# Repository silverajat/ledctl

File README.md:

# ledctl: an FPGA music-sync LED controller

A board I designed from scratch that turns music into a light show on a 115-LED addressable strip.
The laptop listens to what's playing (Spotify or anything else), works out the beat, the bars, the drums,
the genre and where the song is going (build-up, drop, breakdown), and a lighting "director" picks looks the
way a club lighting operator would. Every frame goes to the board, and the FPGA drives the strip.

I built every part of it: the 4-layer PCB, the FPGA logic, the ESP32 firmware, the real-time audio analysis and a phone app.

**Built with:** KiCad · Verilog (Yosys, nextpnr, Icarus) · ESP32-C3 (C++, Arduino) · Python (NumPy, ONNX
Runtime) · Android (Java) · OpenSCAD

*The strip around my pinboard, synced to a song: the build-up, one dark beat, then the drop.*

*The ledctl v1 board: 100 × 62 mm, 4 layers, assembled by JLCPCB.*

---

## What it does

- **Lights it like a club LJ would.** The beat goes into movement and colour (bars snapping to
  new positions, colours bouncing between two opposite hues, sweeps, step chases) while brightness only
  follows the size of the section. The strip is treated as 8 virtual fixtures; one base colour, one moving
  layer and at most one accent at a time.
- **Knows the shape of a song.** Looks hold for a phrase and vary every 4 bars. Build-ups close in from the
  ends and double their step rate, the beat before a drop goes dark, and the drop hits on the beat.
- **Plans songs it has heard before.** Every song is recorded locally and analysed offline (beats, bars,
  sections, drops). When it plays again, the live audio is matched against the recording (one FFT over the
  whole song, level-independent, follows seeks), so drops land exactly and the build-up starts on time.
- **Colours follow the harmony.** A neural network ([YAMNet](https://tfhub.dev/google/yamnet/1)) picks the
  colour family (R&B, hip-hop, EDM, pop, rock, chill), the key picks the palette, and the bass note's place
  in the key picks which colour leads, so the same song always gets the same colours and they move with the
  chords. Grey and white are never sent to the strip.
- **Cinema mode for films, YouTube and games.** It switches automatically when it hears speech or film
  sounds, and stays there while a video site or player is in front. The strip takes the scene's main
  colours from the laptop screen, the way Hue Sync lights a room (or edge by edge, Ambilight-style, for
  a strip around the screen); white becomes a dim tint. Dialogue keeps it calm, the score swells it, music
  with a beat sends waves on the beat, and explosions send one accent in the scene's own colour.
- **A second light with its own role.** A plain (non-addressable) star string on the board's spare MOSFET
  output, dimmed by the FPGA and used like a club rig's extra lamps: almost off in verses, kick hits with a
  warm afterglow, a strobe that speeds up through the build-up, alone at full on the dark beat (a
  blinder), then pumping against every kick after the drop. In films: lightning on impacts.
- **Learns your taste.** An A/B mode shows two versions of the same moment side by side. Your picks are
  saved per genre and the director follows them.
- **Runs without the laptop.** The phone app (Bluetooth) and the board's own modes (solid, breathe, party,
  study timer, ...) work on their own.

## How it fits together

```mermaid
flowchart LR
    subgraph Laptop
        A[System audio<br/>WASAPI loopback] --> B[Analysis<br/>beats, bars, drums,<br/>key, sections]
        Y[YAMNet<br/>genre / mood] --> D
        B --> D[Director<br/>+ effect engine]
        D --> W[Light bench<br/>web page]
    end
    D -- "frames over USB<br/>(checksummed, 60 fps)" --> E
    P[Phone app] -- Bluetooth LE --> E
    subgraph Board
        E[ESP32-C3<br/>BLE / Wi-Fi / USB] -- "1 Mbaud UART" --> F[Gowin GW2AR-18 FPGA]
        E -- "JTAG: loads the FPGA<br/>at every power-up" --> F
        F -- "WS2812B data" --> S[115-LED strip]
        F -- "26 kHz PWM via<br/>low-side MOSFET" --> T[Star string]
        I[INA219<br/>current sensor] --> E
    end
```

| Part | Job |
|---|---|
| **Gowin GW2AR-18 FPGA** | WS2812B driver, double-buffered frame memory, command parser, audio front end (I2S mic, filter bank, beat detector) |
| **ESP32-C3** | Configures the FPGA over JTAG at boot, Bluetooth LE and Wi-Fi control, USB link to the laptop, current limiting |
| **INA219** | Measures the strip's current; the firmware scales frames down if it goes over the limit |
| **Laptop (Python)** | The music brain: analysis, genre network, director, light bench, scoring and tuning tools |

## The hardware

- 4-layer, 100 × 62 mm board, designed in KiCad. ERC/DRC clean.
- Gowin GW2AR-LV18 (QN88), ESP32-C3-MINI-1, 27 MHz clock, 2 MB SPI flash, INA219 current sensor,
  I2S MEMS mic + analog mic, three MOSFET strip outputs, USB-C with ESD protection and a 2.6 A fuse.
- A socket for a [Tiny Tapeout](https://tinytapeout.com) chip, for the phase-2 plan of designing my own
  analog front end in silicon.
- Fab files (Gerbers, BOM, pick-and-place) in [`hardware/fab`](hardware/fab), and a 3D-printable
  enclosure in [`hardware/enclosure`](hardware/enclosure).

## The FPGA design ([`fpga/v2`](fpga/v2))

- **WS2812B driver.** 800 kHz, GRB, cycle-exact at 27 MHz (0.41 / 0.81 µs high times, 1.26 µs bits,
  300 µs latch). Output straight from an FPGA pin.
- **Frame packets** from the ESP32 at 1 Mbaud: `0xA7, n_lo, n_hi, n × RGB`, written into one bank of a
  double-buffered block RAM while the other bank is shown. The parser resyncs after a gap.
- **Fallback.** With no frames for 1 s the strip shows the board's own colour, so the phone modes keep
  working.
- **UART input with a glitch filter** (the line only changes after 5 equal samples) against crosstalk from
  the strip pins next to it.
- **Star PWM** on two spare MOSFET outputs: set by a 5-byte command, 8-bit duty at ~26 kHz from a
  set/reset flop, forced off when frames stop. The laptop sends the level as one extra pixel after the
  strip, and the ESP32 turns it into the command.
- **Diagnostics in the telemetry:** packets received, strip refreshes sent, the star levels the FPGA holds,
  and its live flags (frames arriving, strip mode, the state of each output pin). The laptop shows them all,
  so the whole path from the music brain to an output pin can be checked without a scope.
- The v1 audio front end is still in there: I2S receiver, IIR 3-band filter bank with log envelopes,
  beat detector, telemetry to the ESP32 every 10 ms.
- Open toolchain only: Yosys, nextpnr-himbaechel, gowin_pack. Testbenches in Icarus Verilog
  (`tb_ws.v`, `tb_boot.v`, `tb_glitch.v`, `tb_stars.v`). About 28% of the FPGA's LUTs.

## The music brain ([`laptop/musicbrain`](laptop/musicbrain))

**Analysis** (`analysis.py`, all causal, ~10 ms hops, about 1 ms per hop):
- 40 mel bands, each normalised to its own recent range
- kick / snare / hi-hat detectors on per-band spectral flux with adaptive thresholds
- tempo from an autocorrelation with harmonic scoring and a genre-aware prior; beat phase from a PLL on a
  continuous beat position, so corrections never add or drop beats
- bar lines from chord changes, bass-note changes and kicks, minus backbeat snares
- key (Krumhansl), lead pitch, voice level and stereo position
- sections from novelty spikes on downbeats; build-ups from steady rises with the bass held back;
  drops from the kick and full bass returning
- a harmonic/percussive split (median filtering over time), stereo balance, risers (rising, noisier top
  end) and impacts (big broadband hits)

**Director and effects** (`show.py`): 12 looks (wash, bass floor, colour bounce, stripes, sweep, step
chase, scanners, stereo split, punch, swell, peak, build) in three styles (smooth, punchy, club), chosen
by the size of the music and held for phrases; snare wipes and impact ripples as rate-limited accents;
harmony-driven colours; brightness per section; hue-preserving limits and a power limit for the strip.
This file is also the reference model for moving the effect engine into the FPGA.

**Known songs** (`songmap.py`): finds the position in a recorded song by cosine similarity of the
spectral shape at every offset (one FFT), locks after two agreeing matches (about 10 s, ~3 ms error),
and lays the song's real beat grid, sections and upcoming drops over the live analysis.

**Cinema** (`cinema.py`): screen capture through GDI (no extra installs); in the room layout the scene's
2-3 main colours from a saturation-weighted hue histogram, eased around the colour wheel (never through
grey); in the screen layout one colour per screen edge; cut-aware smoothing; sound states (dialogue,
score, music on the beat) smoothed over seconds with hysteresis; impact accents; subtle, normal and
intense settings; a black (DRM-protected) picture falls back to mood colours.

**Teaching it:**
- **Light bench:** a web page with a virtual strip, a 10 s timeline of what the brain heard, and
  "looks right / looks wrong" buttons that save the last 10 s of state.
- **A/B taste test:** two strips, one thing different, blind left/right; picks are saved per genre.
- **Scoring:** `truth.py` works out reference beats and bar lines offline with
  [Beat This!](https://github.com/CPJKU/beat_this) and sections from self-similarity; `tools/score.py`
  replays recordings through the live brain and scores it, and `tools/tune.py` searches its settings.

*A build-up and drop on a synthetic test track, drawn as the strip over time (left to right = 40 s → 70 s,
LEDs top to bottom): mirrored sweeps in the verse; in the build-up the lights close in from the ends while
the steps speed up and the colours spin; one dark beat; then the drop: mirrored blocks changing colour on
every beat with scanners crossing over them.*

## Bring-up: what broke and how I fixed it

The full log is in [`docs/bringup.md`](docs/bringup.md). The short version:

1. **The FPGA's flash couldn't be written** through the programmer. I wrote a JTAG loader for the ESP32
   from Gowin's programming spec, so the board loads the FPGA itself at every power-up.
2. **Music mode didn't react:** an unsigned subtraction bug in the FPGA's loudness filter.
3. **The room fan triggered fake beats:** a gated Kalman filter that learns each band's noise floor.
4. **Spotify shut down its audio-analysis API**, so the laptop analyses its own audio output instead.
5. **The first LED died** during wiring (a mixed-up ground and data line), freezing the whole strip.
   Lesson: ground first, data last.
6. **Strip signal vs. serial link.** The MOSFET output was too slow for the strip at normal drive
   strength, and at high drive its edges corrupted the ESP32 → FPGA link on the neighbouring pin. Moved
   the strip to a direct FPGA pin and added the counters that proved it.
7. **Random colours on the strip but not on screen:** the ESP32's USB receive buffer overflowed at
   18 KB/s. A bigger buffer plus a checksum on every frame fixed it.
8. **The star lights never lit** (except for a second at every power-up). The board's current sensor showed
   no extra draw even at 100%, so I added read-back at every stage (laptop → ESP32 → FPGA register → pin).
   Every stage was right, so the fault was past the board: the wire was on J2 pin 5, the FPGA's JTAG data
   output, which only toggles while the ESP32 loads the FPGA. That also explained the flash at power-up.

## Status and next steps

**Working:** the board, FPGA strip driver, ESP32 firmware, phone app, laptop music brain over USB or
Bluetooth, the LJ-style effect engine, pre-planned shows for known songs, cinema mode, the star string on the
kick, light bench, genre network, A/B taste learning.

**Next:**
- Run the scoring and tuning on a set of recorded songs
- Move the effect engine from Python into the FPGA (`show.py` is the reference model), so the laptop only
  sends a few features per frame
- Firmware updates over Bluetooth (move the FPGA image into its own flash partition first)
- A small int8 beat-detection network on the FPGA for a stand-alone, mic-only mode

## Repository layout

```
hardware/   KiCad project, fab files, enclosure
fpga/       v1 (audio front end) and v2 (strip driver) Verilog, constraints, testbenches
firmware/   ESP32-C3 Arduino sketch, FPGA bitstream converter
android/    phone app (built without Gradle)
laptop/     musicbrain: the laptop music brain (Python)
tools/      DSP tuning simulations
docs/       bring-up log, images
```

## Building

**FPGA** (needs `yowasp-yosys`, `yowasp-nextpnr-himbaechel`, `gowin_pack` from Apicula):
```sh
cd fpga/v2 && ./build.sh            # -> ledctl_v2.fs
```

**Firmware** (Arduino core for ESP32 3.3.x, board "ESP32C3 Dev Module", USB CDC on boot, partition
scheme "Huge APP"):
```sh
python firmware/tools/fs2h.py fpga/v2/ledctl_v2.fs firmware/ledctl/fpga_bits.h   # embed the bitstream
arduino-cli compile --fqbn esp32:esp32:esp32c3:CDCOnBoot=cdc,PartitionScheme=huge_app firmware/ledctl
```

**Music brain** (Windows, Python 3.13):
```sh
cd laptop/musicbrain
pip install numpy pyaudiowpatch onnxruntime pyserial bleak
python brain.py            # opens the light bench at http://localhost:8766
```

**Wiring the strip:** strip GND → J2 pin 2, strip 5V → J4 pin 1, strip DIN → J3 pin 3 (FPGA pin 48).
Connect ground first.

## Credits and licences

My own work is under the MIT licence ([LICENSE](LICENSE)).
`laptop/musicbrain/ml/yamnet.onnx` is Google's YAMNet, converted to ONNX, under the Apache 2.0 licence.
Beat This! (CPJKU) is used offline for reference beats and is not included.

Rajat Gupta, NUS Electrical Engineering

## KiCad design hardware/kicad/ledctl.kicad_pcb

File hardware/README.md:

# Hardware (ledctl v1)

- `kicad/`: KiCad project (schematic, 4-layer PCB, custom symbols and footprints)
- `fab/`: what went to JLCPCB: Gerbers, BOM, pick-and-place, schematic PDF, FPGA pin constraints
- `enclosure/`: OpenSCAD source and STL files for a two-part box

## Connectors
| Header | Pins |
|---|---|
| **J2** JTAG (1×6) | 1 3V3 · **2 GND** · 3 TCK · 4 TDI · 5 TDO · 6 TMS |
| **J3** expansion (2×5, not fitted) | 1 3V3 · **2 GND** · **3 FPGA pin 48 (strip data)** · 4–10 more FPGA I/O |
| **J4** strip (1×4) | **1 +5V** (after the current sensor) · 2 G · 3 R · 4 B (low-side MOSFETs) |

**Wiring a WS2812B strip:** GND → J2 pin 2 (or J3 pin 2), 5V → J4 pin 1, DIN → J3 pin 3.
Connect ground first and data last. Power comes from USB-C through a 2.6 A fuse; the firmware limits the strip
to about 2 A.

## Known notes
- J4 pins 2 and 4 drive the star string (a plain LED string between J4 pin 1 and pin 4, with a series
  resistor). Don't confuse J4 with J2: J2 pin 5 is the FPGA's JTAG TDO.
- J4's outputs are open-drain MOSFETs. For WS2812B data they need a pull-up and switch too slowly at normal
  drive strength, so the strip uses J3 instead (see `docs/bringup.md`).
- MK2's ground ring is 0.16 mm from its sound hole (fixed in the source for v2; no effect on these boards).

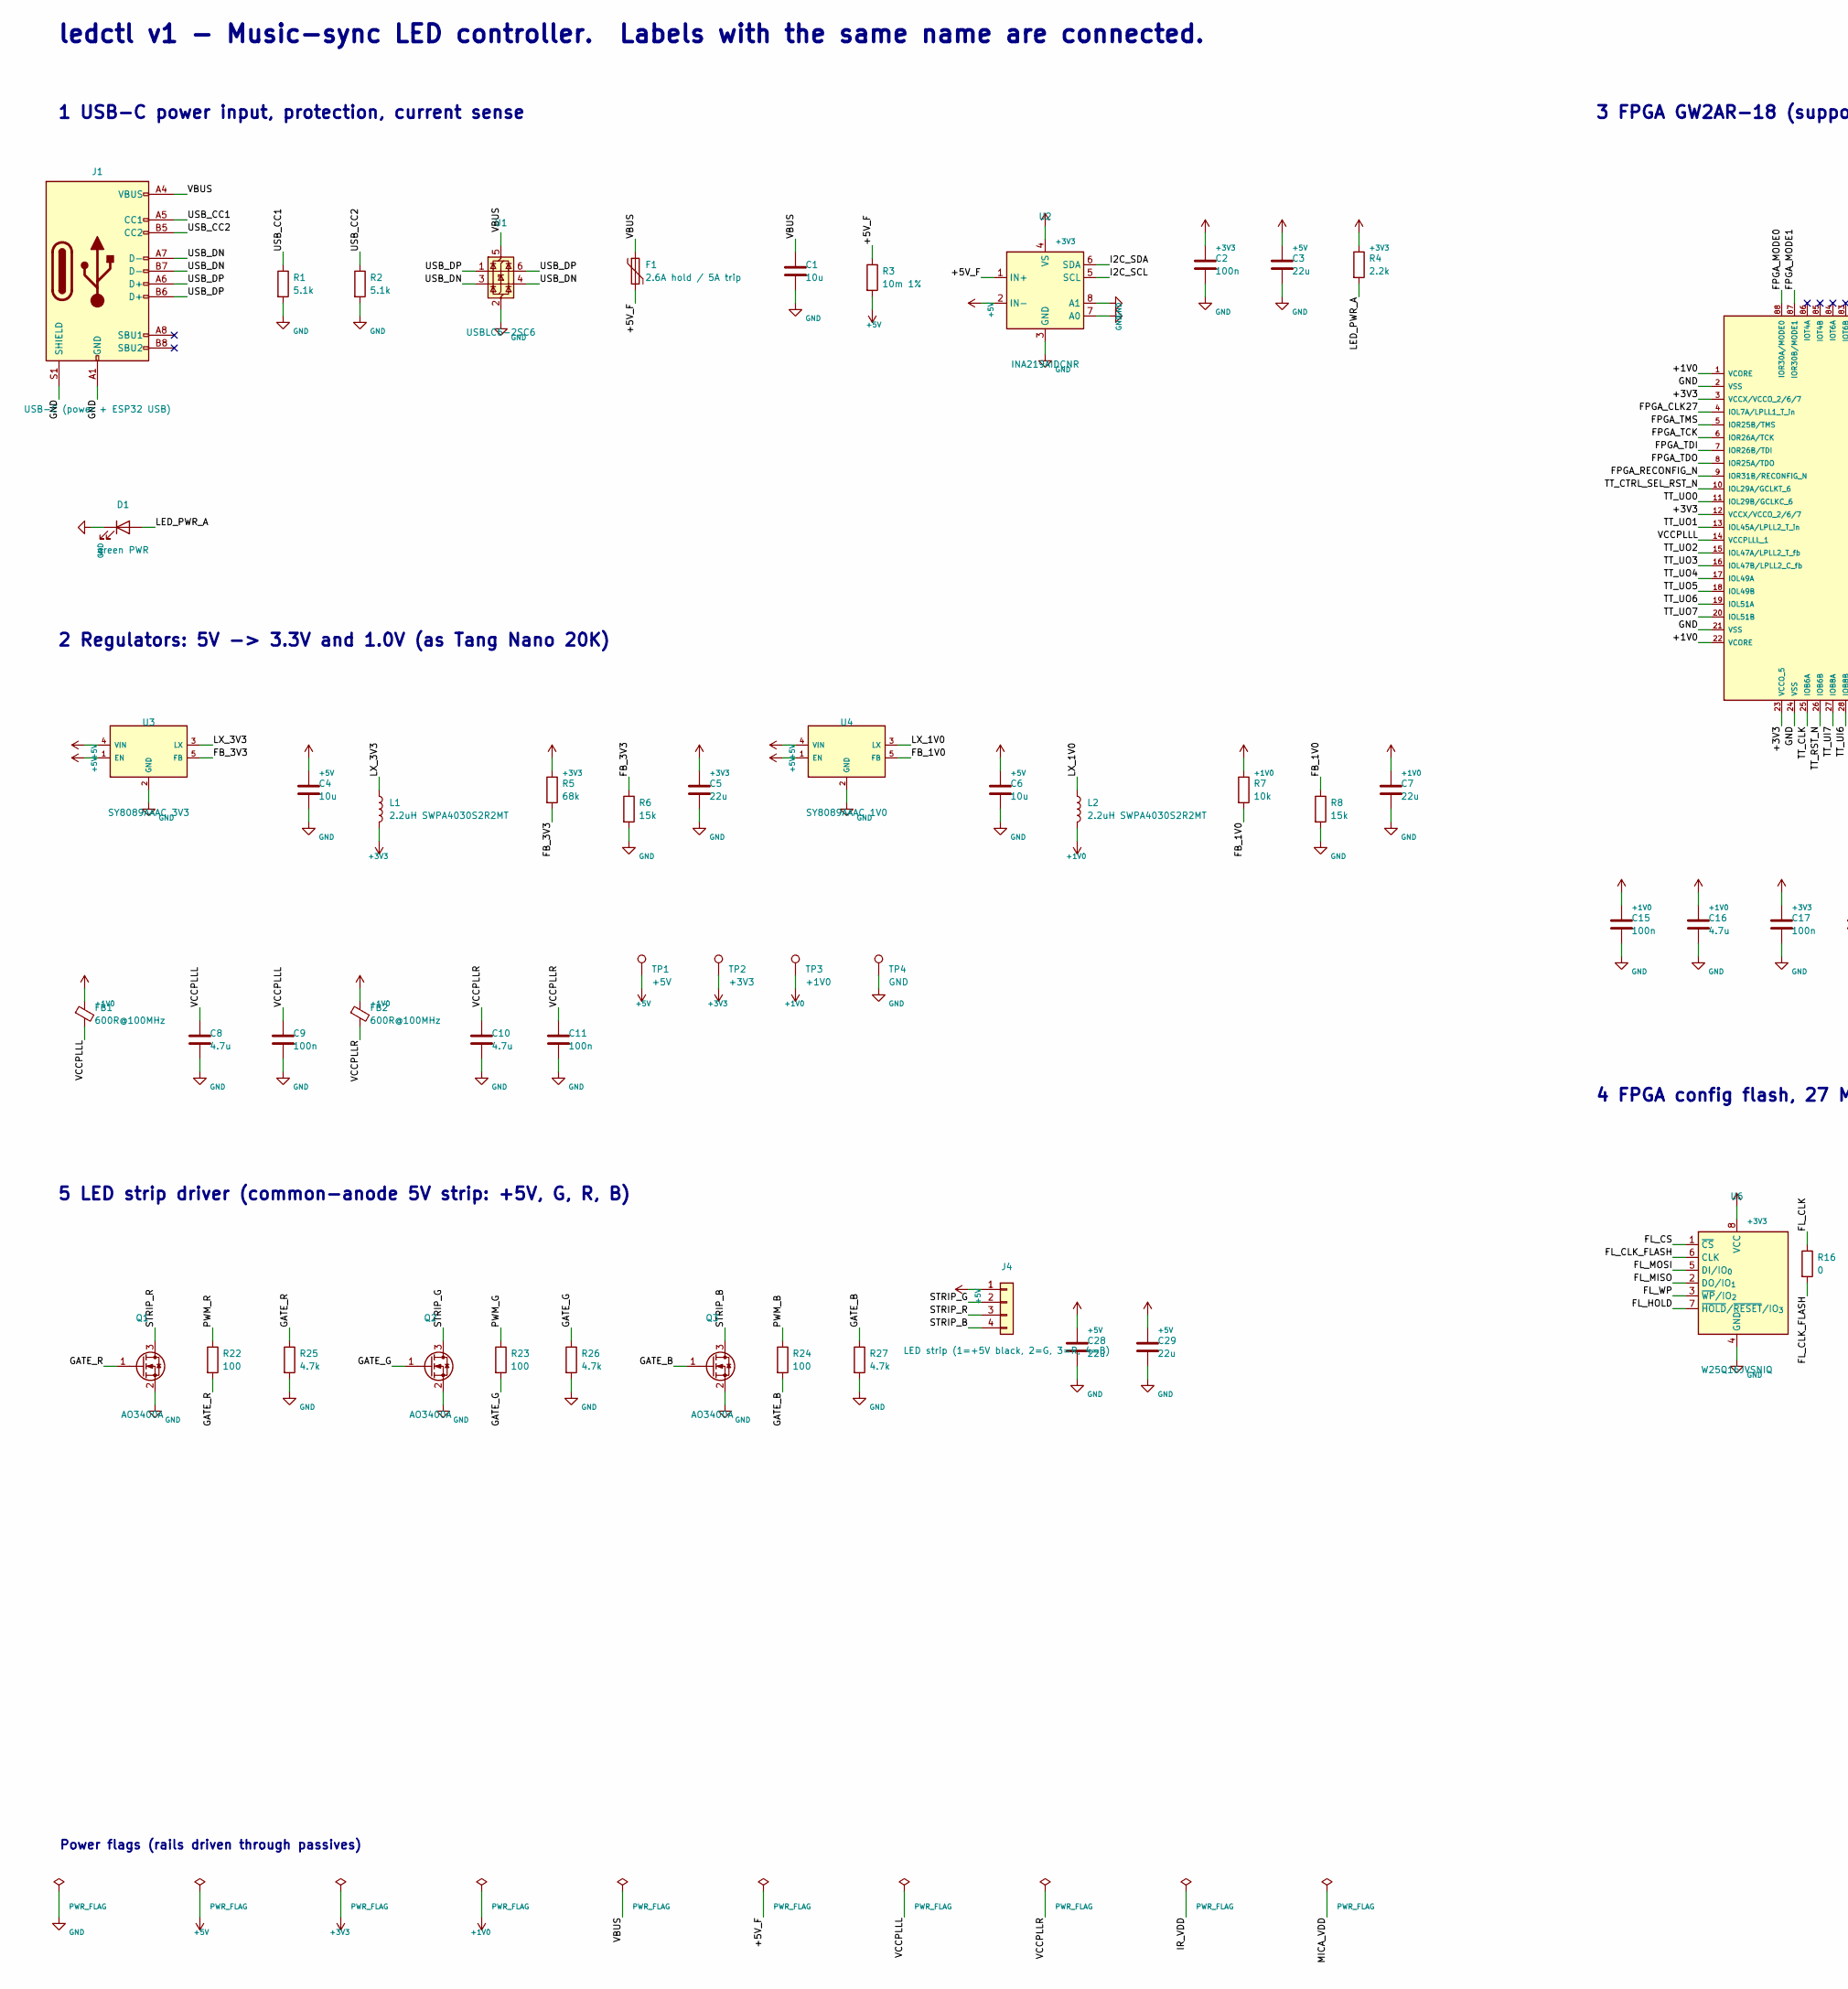
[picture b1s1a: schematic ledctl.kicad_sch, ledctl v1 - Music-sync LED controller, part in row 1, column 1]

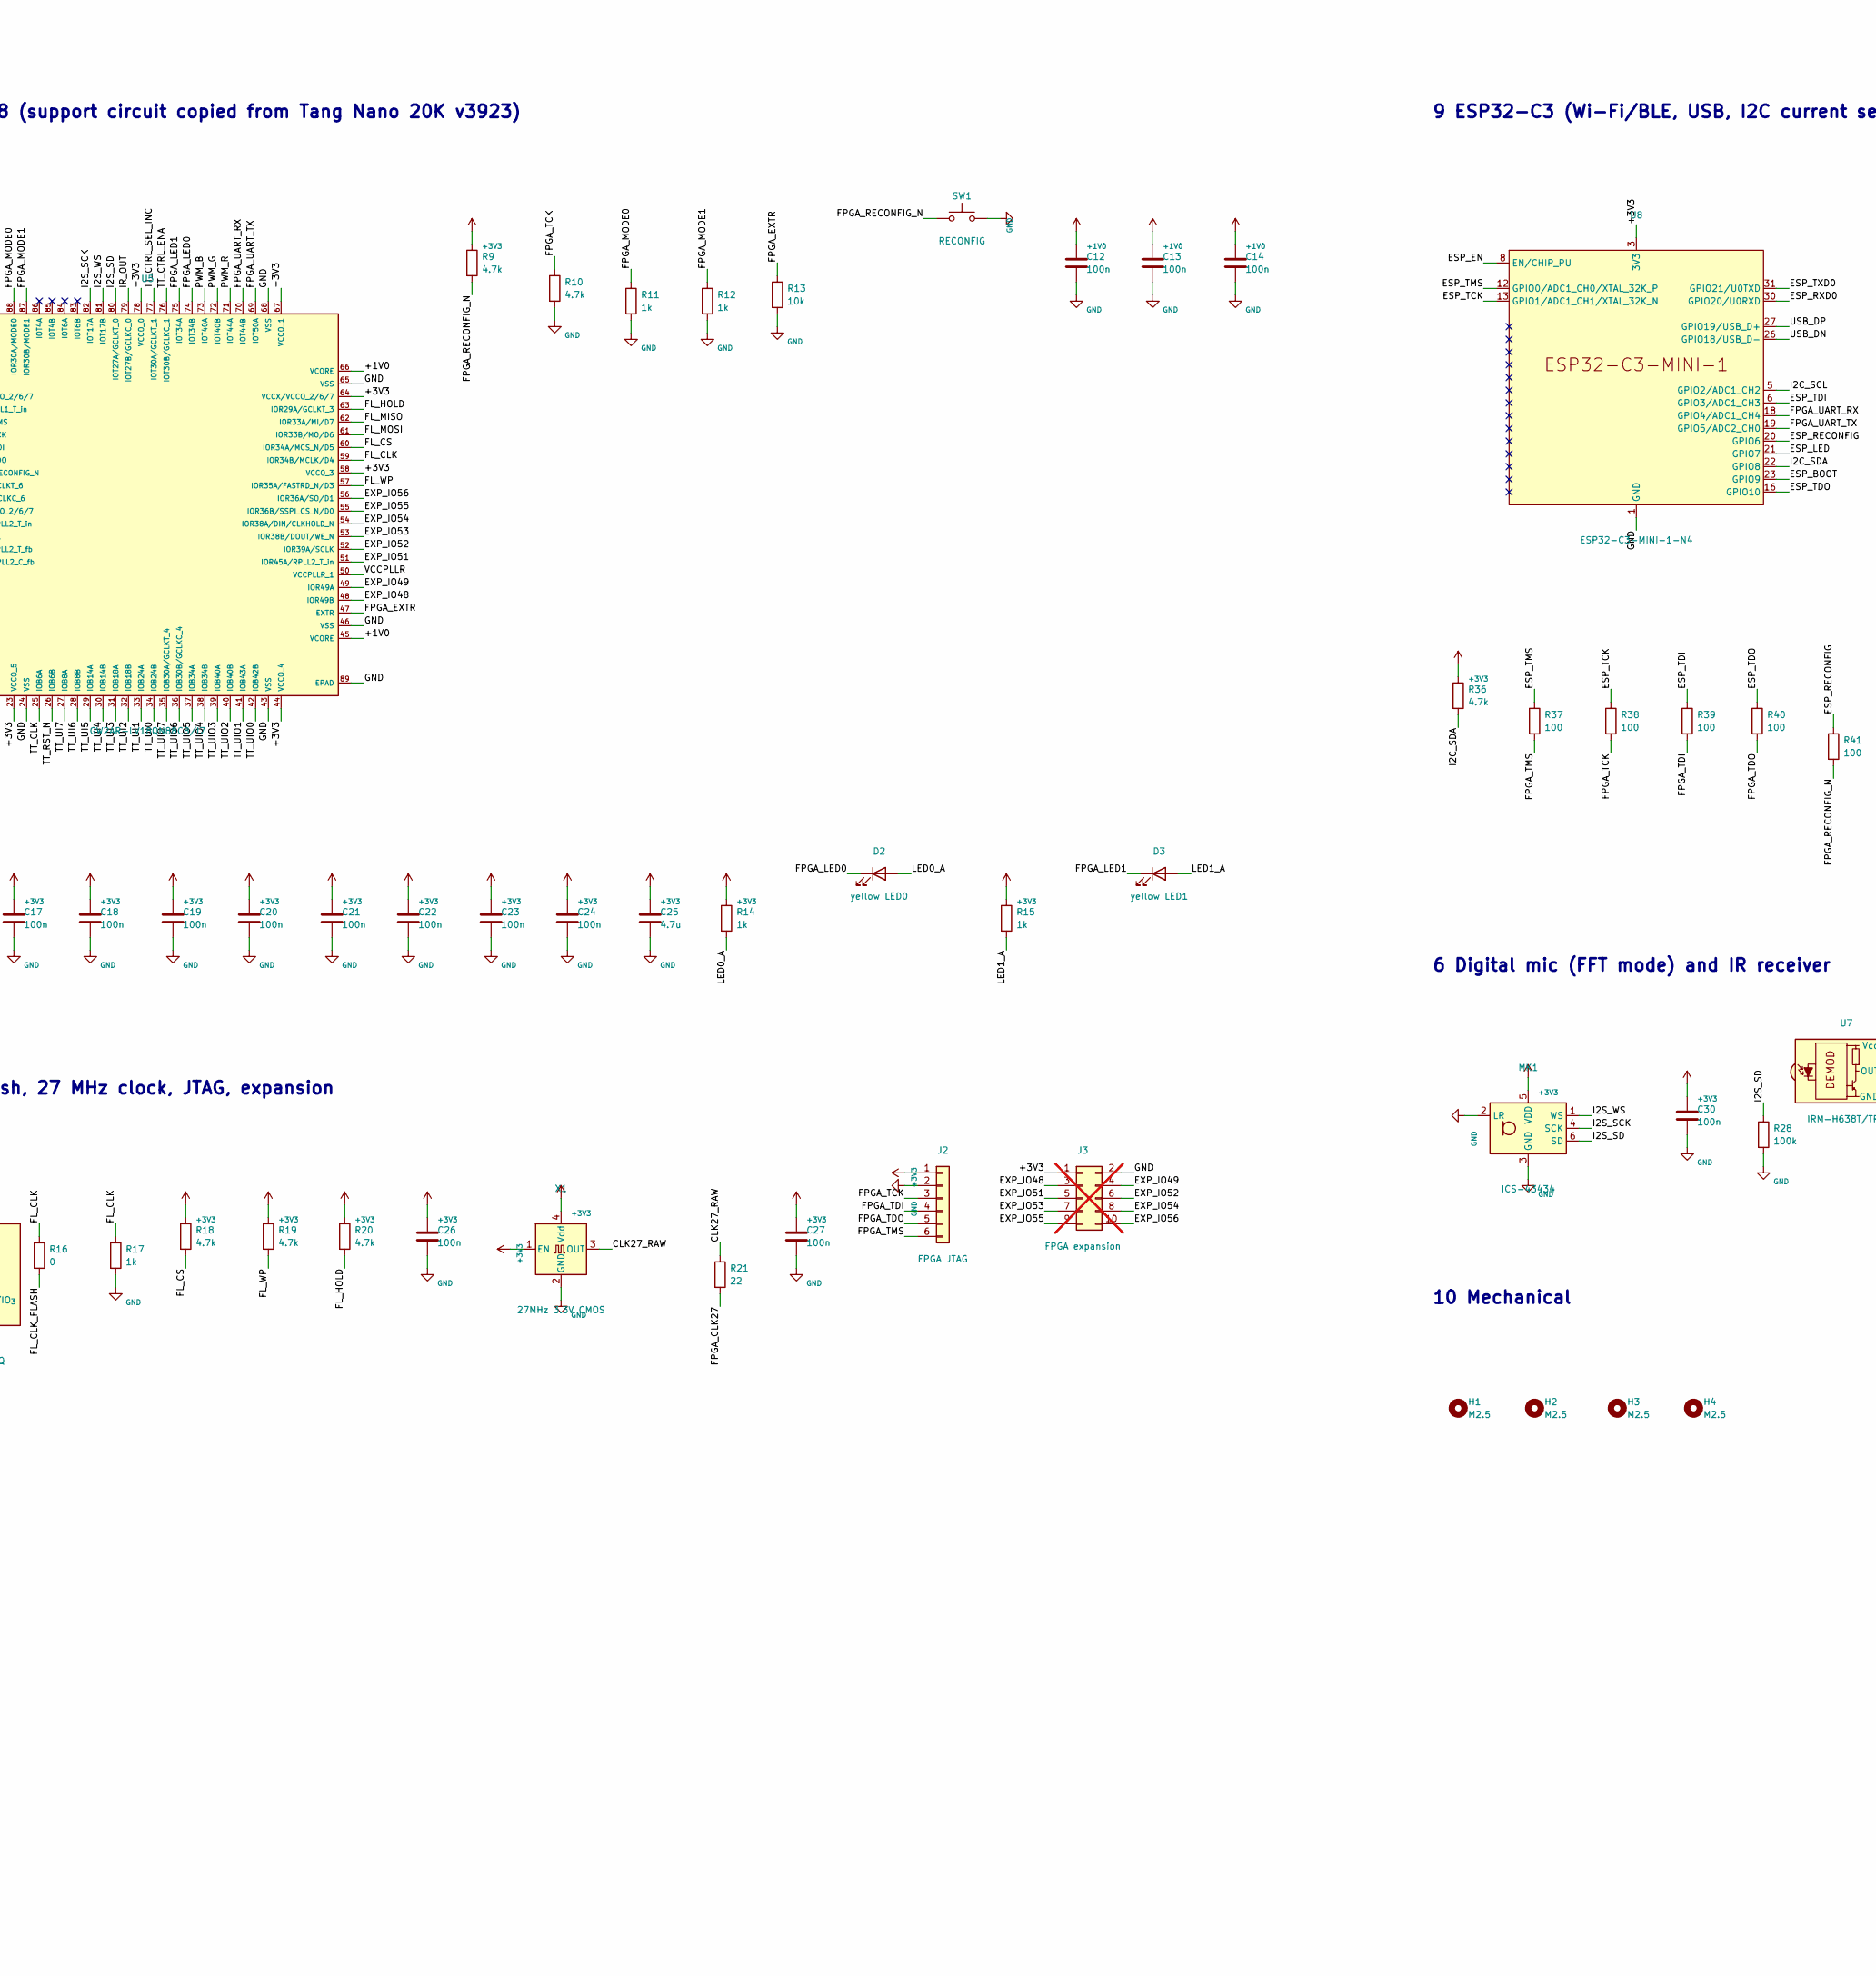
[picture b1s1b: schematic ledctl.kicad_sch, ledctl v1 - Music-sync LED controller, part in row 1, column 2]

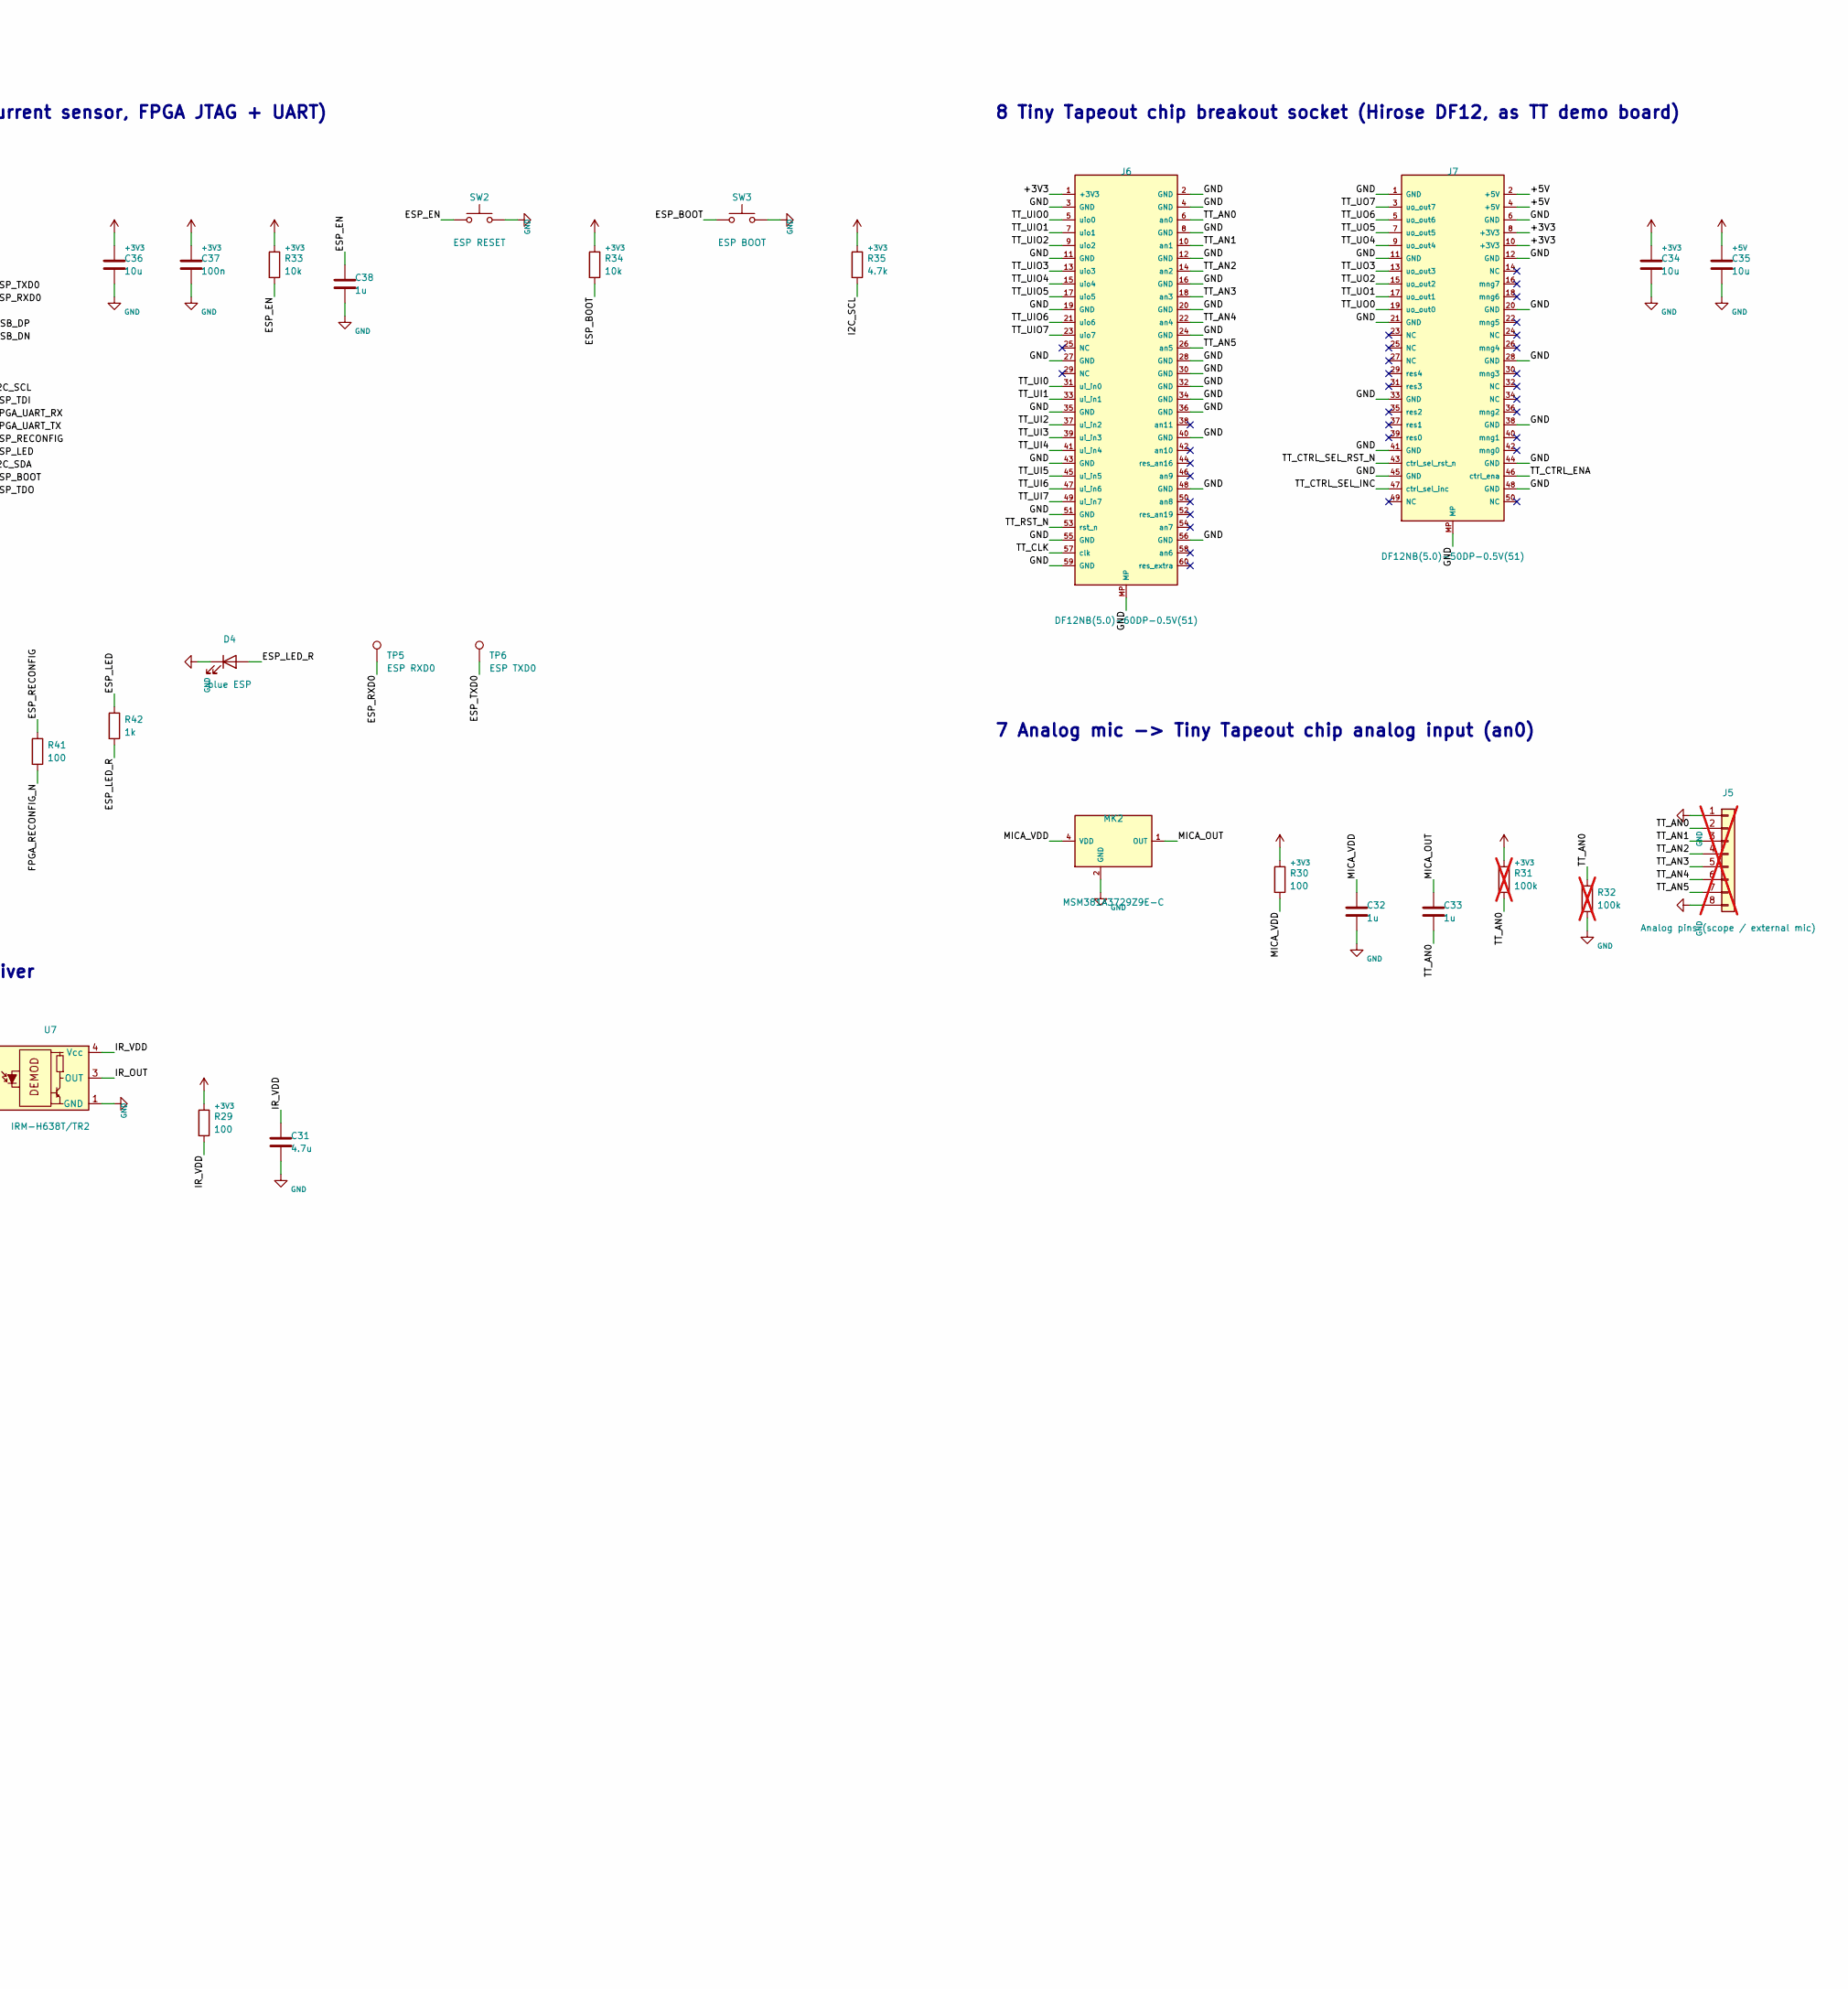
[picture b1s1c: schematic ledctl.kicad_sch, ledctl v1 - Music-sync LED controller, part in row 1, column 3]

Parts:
C1, C4, C6, C34, C35, C36: 10u; C_0603_1608Metric; LCSC C19702
C2, C9, C11, C12, C13, C14, C15, C17, C18, C19, C20, C21, C22, C23, C24, C26, C27, C30, C37: 100n; C_0402_1005Metric; LCSC C1525
C3, C5, C7, C28, C29: 22u; C_0805_2012Metric; LCSC C45783
C8, C10, C16, C25, C31: 4.7u; C_0603_1608Metric; LCSC C19666
C32, C33, C38: 1u; C_0402_1005Metric; LCSC C52923
D1: green PWR; LED_0603_1608Metric; LCSC C72043
D2: yellow LED0; LED_0603_1608Metric; LCSC C72038
D3: yellow LED1; LED_0603_1608Metric; LCSC C72038
D4: blue ESP; LED_0603_1608Metric; LCSC C72041
F1: 2.6A hold / 5A trip; Fuse_1812_4532Metric; LCSC C20814
FB1, FB2: 600R@100MHz; L_0603_1608Metric; LCSC C1002
H1, H2, H3, H4: M2.5; MountingHole_2.7mm_M2.5
J1: USB-C (power + ESP32 USB); USB_C_Receptacle_HRO_TYPE-C-31-M-12; LCSC C165948
J2: FPGA JTAG; PinHeader_1x06_P2.54mm_Vertical; LCSC C42431790
J3: FPGA expansion; PinHeader_2x05_P2.54mm_Vertical; LCSC C225520; not fitted
J4: LED strip (1=+5V black, 2=G, 3=R, 4=B); PinSocket_1x04_P2.54mm_Vertical; LCSC C2718488
J5: Analog pins (scope / external mic); PinHeader_1x08_P2.54mm_Vertical; not fitted
J6: DF12NB(5.0)-60DP-0.5V(51); Hirose_DF12NB5.0-60DP_TT; LCSC C2847989
J7: DF12NB(5.0)-50DP-0.5V(51); Hirose_DF12NB5.0-50DP_TT; LCSC C3020266
L1, L2: 2.2uH SWPA4030S2R2MT; L_Sunlord_SWPA4030S; LCSC C36409
MK1: ICS-43434; InvenSense_ICS-43434-6_3.5x2.65mm; LCSC C5656610
MK2: MSM381A3729Z9E-C; MEMSensing_LGA-6_2.95x3.76mm; LCSC C51928206
Q1, Q2, Q3: AO3400A; SOT-23; LCSC C20917
R1, R2: 5.1k; R_0402_1005Metric; LCSC C25905
R3: 10m 1%; R_1206_3216Metric; LCSC C601097
R4: 2.2k; R_0402_1005Metric; LCSC C25879
R5: 68k; R_0402_1005Metric; LCSC C36871
R6, R8: 15k; R_0402_1005Metric; LCSC C25756
R7, R13, R33, R34: 10k; R_0402_1005Metric; LCSC C25744
R9, R10, R18, R19, R20, R25, R26, R27, R35, R36: 4.7k; R_0402_1005Metric; LCSC C25900
R11, R12, R14, R15, R17, R42: 1k; R_0402_1005Metric; LCSC C11702
R16: 0; R_0402_1005Metric; LCSC C17168
R21: 22; R_0402_1005Metric; LCSC C25092
R22, R23, R24, R29, R30, R37, R38, R39, R40, R41: 100; R_0402_1005Metric; LCSC C25076
R28: 100k; R_0402_1005Metric; LCSC C25741
R31, R32: 100k; R_0402_1005Metric; LCSC C25741; not fitted
SW1: RECONFIG; SW_Push_1P1T_XKB_TS-1187A; LCSC C318884
SW2: ESP RESET; SW_Push_1P1T_XKB_TS-1187A; LCSC C318884
SW3: ESP BOOT; SW_Push_1P1T_XKB_TS-1187A; LCSC C318884
TP1: +5V; TestPoint_Pad_D1.0mm
TP2: +3V3; TestPoint_Pad_D1.0mm
TP3: +1V0; TestPoint_Pad_D1.0mm
TP4: GND; TestPoint_Pad_D1.0mm
TP5: ESP RXD0; TestPoint_Pad_D1.0mm
TP6: ESP TXD0; TestPoint_Pad_D1.0mm
U1: USBLC6-2SC6; SOT-23-6; LCSC C7519
U2: INA219AIDCNR; SOT-23-8; LCSC C87469
U3: SY8089AAAC 3V3; SOT-23-5; LCSC C78988
U4: SY8089AAAC 1V0; SOT-23-5; LCSC C78988
U5: GW2AR-LV18QN88C8/I7; QFN-88-1EP_10x10mm_P0.4mm_EP6.74x6.74mm; LCSC C380550
U6: W25Q16JVSNIQ; SOIC-8_3.9x4.9mm_P1.27mm; LCSC C2456211
U7: IRM-H638T/TR2; Everlight_IRM-H6xxT; LCSC C91447
U8: ESP32-C3-MINI-1-N4; ESP32-C3-MINI-1; LCSC C2838502
X1: 27MHz 3.3V CMOS; Oscillator_SMD_Abracon_ASE-4Pin_3.2x2.5mm; LCSC C22434870

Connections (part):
+1V0: C7.1, C12.1, C13.1, C14.1, C15.1, C16.1, FB1.1, FB2.1, L2.2, R7.1, TP3.1, U5.1 (VCORE), U5.22 (VCORE), U5.45 (VCORE), U5.66 (VCORE)
+3V3: C2.1, C5.1, C17.1, C18.1, C19.1, C20.1, C21.1, C22.1, C23.1, C24.1, C25.1, C26.1, C27.1, C30.1, C34.1, C36.1, C37.1, J2.1, J3.1, J6.1 (+3V3), J7.8 (+3V3), J7.10 (+3V3), L1.2, MK1.5 (VDD), R4.1, R5.1, R9.1, R14.1, R15.1, R18.1, R19.1, R20.1, R29.1, R30.1, R31.1, R33.1, R34.1, R35.1, R36.1, TP2.1, U2.4 (VS), U5.3 (VCCX/VCCO_2/6/7), U5.12 (VCCX/VCCO_2/6/7), U5.23 (VCCO_5), U5.44 (VCCO_4), U5.58 (VCCO_3), U5.64 (VCCX/VCCO_2/6/7), U5.67 (VCCO_1), U5.78 (VCCO_0), U6.8 (VCC), U8.3 (3V3), X1.1 (EN), X1.4 (Vdd)
+5V: C3.1, C4.1, C6.1, C28.1, C29.1, C35.1, J4.1, J7.2 (+5V), J7.4 (+5V), R3.2, TP1.1, U2.2 (IN-), U3.1 (EN), U3.4 (VIN), U4.1 (EN), U4.4 (VIN)
+5V_F: F1.2, R3.1, U2.1 (IN+)
CLK27_RAW: R21.1, X1.3 (OUT)
ESP_BOOT: R34.2, SW3.1, U8.23 (GPIO9)
ESP_EN: C38.1, R33.2, SW2.1, U8.8 (EN/CHIP_PU)
ESP_LED: R42.1, U8.21 (GPIO7)
ESP_LED_R: D4.2 (A), R42.2
ESP_RECONFIG: R41.1, U8.20 (GPIO6)
ESP_RXD0: TP5.1, U8.30 (GPIO20/U0RXD)
ESP_TCK: R38.1, U8.13 (GPIO1/ADC1_CH1/XTAL_32K_N)
ESP_TDI: R39.1, U8.6 (GPIO3/ADC1_CH3)
ESP_TDO: R40.1, U8.16 (GPIO10)
ESP_TMS: R37.1, U8.12 (GPIO0/ADC1_CH0/XTAL_32K_P)
ESP_TXD0: TP6.1, U8.31 (GPIO21/U0TXD)
EXP_IO48: J3.3, U5.48 (IOR49B)
EXP_IO49: J3.4, U5.49 (IOR49A)
EXP_IO51: J3.5, U5.51 (IOR45A/RPLL2_T_in)
EXP_IO52: J3.6, U5.52 (IOR39A/SCLK)
EXP_IO53: J3.7, U5.53 (IOR38B/DOUT/WE_N)
EXP_IO54: J3.8, U5.54 (IOR38A/DIN/CLKHOLD_N)
EXP_IO55: J3.9, U5.55 (IOR36B/SSPI_CS_N/D0)
EXP_IO56: J3.10, U5.56 (IOR36A/SO/D1)
FB_1V0: R7.2, R8.1, U4.5 (FB)
FB_3V3: R5.2, R6.1, U3.5 (FB)
FL_CLK: R16.1, R17.1, U5.59 (IOR34B/MCLK/D4)
FL_CLK_FLASH: R16.2, U6.6 (CLK)
FL_CS: R18.2, U5.60 (IOR34A/MCS_N/D5), U6.1 (~CS)
FL_HOLD: R20.2, U5.63 (IOR29A/GCLKT_3), U6.7 (~HOLD/~RESET/IO_{3})
FL_MISO: U5.62 (IOR33A/MI/D7), U6.2 (DO/IO_{1})
FL_MOSI: U5.61 (IOR33B/MO/D6), U6.5 (DI/IO_{0})
FL_WP: R19.2, U5.57 (IOR35A/FASTRD_N/D3), U6.3 (~WP/IO_{2})
FPGA_CLK27: R21.2, U5.4 (IOL7A/LPLL1_T_in)
FPGA_EXTR: R13.1, U5.47 (EXTR)
FPGA_LED0: D2.1 (K), U5.74 (IOT34B)
FPGA_LED1: D3.1 (K), U5.75 (IOT34A)
FPGA_MODE0: R11.1, U5.88 (IOR30A/MODE0)
FPGA_MODE1: R12.1, U5.87 (IOR30B/MODE1)
FPGA_RECONFIG_N: R9.2, R41.2, SW1.1, U5.9 (IOR31B/RECONFIG_N)
FPGA_TCK: J2.3, R10.1, R38.2, U5.6 (IOR26A/TCK)
FPGA_TDI: J2.4, R39.2, U5.7 (IOR26B/TDI)
FPGA_TDO: J2.5, R40.2, U5.8 (IOR25A/TDO)
FPGA_TMS: J2.6, R37.2, U5.5 (IOR25B/TMS)
FPGA_UART_RX: U5.70 (IOT44B), U8.18 (GPIO4/ADC1_CH4)
FPGA_UART_TX: U5.69 (IOT50A), U8.19 (GPIO5/ADC2_CH0)
GATE_B: Q3.1 (G), R24.2, R27.1
GATE_G: Q2.1 (G), R23.2, R26.1
GATE_R: Q1.1 (G), R22.2, R25.1
GND: C1.2, C2.2, C3.2, C4.2, C5.2, C6.2, C7.2, C8.2, C9.2, C10.2, C11.2, C12.2, C13.2, C14.2, C15.2, C16.2, C17.2, C18.2, C19.2, C20.2, C21.2, C22.2, C23.2, C24.2, C25.2, C26.2, C27.2, C28.2, C29.2, C30.2, C31.2, C32.2, C34.2, C35.2, C36.2, C37.2, C38.2, D1.1 (K), D4.1 (K), J1.A1 (GND), J1.A12 (GND), J1.B1 (GND), J1.B12 (GND), J1.S1 (SHIELD), J2.2, J3.2, J5.1, J5.8, J6.2 (GND), J6.3 (GND), J6.4 (GND), J6.8 (GND), J6.11 (GND), J6.12 (GND), J6.16 (GND), J6.19 (GND), J6.20 (GND), J6.24 (GND), J6.27 (GND), J6.28 (GND), J6.30 (GND), J6.32 (GND), J6.34 (GND), J6.35 (GND), J6.36 (GND), J6.40 (GND), J6.43 (GND), J6.48 (GND), J6.51 (GND), J6.55 (GND), J6.56 (GND), J6.59 (GND), J6.MP, J7.1 (GND), J7.6 (GND), J7.11 (GND), J7.12 (GND), J7.20 (GND), J7.21 (GND), J7.28 (GND), J7.33 (GND), J7.38 (GND), J7.41 (GND), J7.44 (GND), J7.45 (GND), J7.48 (GND), J7.MP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
I2C_SCL: R35.2, U2.5 (SCL), U8.5 (GPIO2/ADC1_CH2)
I2C_SDA: R36.2, U2.6 (SDA), U8.22 (GPIO8)
I2S_SCK: MK1.4 (SCK), U5.82 (IOT17A)
I2S_SD: MK1.6 (SD), R28.1, U5.80 (IOT27A/GCLKT_0)
I2S_WS: MK1.1 (WS), U5.81 (IOT17B)
IR_OUT: U5.79 (IOT27B/GCLKC_0), U7.3 (OUT)
IR_VDD: C31.1, R29.2, U7.4 (Vcc)
LED0_A: D2.2 (A), R14.2
LED1_A: D3.2 (A), R15.2
LED_PWR_A: D1.2 (A), R4.2
LX_1V0: L2.1, U4.3 (LX)
LX_3V3: L1.1, U3.3 (LX)
MICA_OUT: C33.1, MK2.1 (OUT)
MICA_VDD: C32.1, MK2.4 (VDD), R30.2
PWM_B: R24.1, U5.73 (IOT40A)
PWM_G: R23.1, U5.72 (IOT40B)
PWM_R: R22.1, U5.71 (IOT44A)
STRIP_B: J4.4, Q3.3 (D)
STRIP_G: J4.2, Q2.3 (D)
STRIP_R: J4.3, Q1.3 (D)
TT_AN0: C33.2, J5.2, J6.6 (an0), R31.2, R32.1
TT_AN1: J5.3, J6.10 (an1)
TT_AN2: J5.4, J6.14 (an2)
TT_AN3: J5.5, J6.18 (an3)
TT_AN4: J5.6, J6.22 (an4)
TT_AN5: J5.7, J6.26 (an5)
TT_CLK: J6.57 (clk), U5.25 (IOB6A)
TT_CTRL_ENA: J7.46 (ctrl_ena), U5.76 (IOT30B/GCLKC_1)
TT_CTRL_SEL_INC: J7.47 (ctrl_sel_inc), U5.77 (IOT30A/GCLKT_1)
TT_CTRL_SEL_RST_N: J7.43 (ctrl_sel_rst_n), U5.10 (IOL29A/GCLKT_6)
TT_RST_N: J6.53 (rst_n), U5.26 (IOB6B)
TT_UI0: J6.31 (ui_in0), U5.34 (IOB24B)
TT_UI1: J6.33 (ui_in1), U5.33 (IOB24A)
TT_UI2: J6.37 (ui_in2), U5.32 (IOB18B)
TT_UI3: J6.39 (ui_in3), U5.31 (IOB18A)
TT_UI4: J6.41 (ui_in4), U5.30 (IOB14B)
TT_UI5: J6.45 (ui_in5), U5.29 (IOB14A)
TT_UI6: J6.47 (ui_in6), U5.28 (IOB8B)
TT_UI7: J6.49 (ui_in7), U5.27 (IOB8A)
TT_UIO0: J6.5 (uio0), U5.42 (IOB42B)
TT_UIO1: J6.7 (uio1), U5.41 (IOB43A)
TT_UIO2: J6.9 (uio2), U5.40 (IOB40B)
TT_UIO3: J6.13 (uio3), U5.39 (IOB40A)
TT_UIO4: J6.15 (uio4), U5.38 (IOB34B)
TT_UIO5: J6.17 (uio5), U5.37 (IOB34A)
TT_UIO6: J6.21 (uio6), U5.36 (IOB30B/GCLKC_4)
TT_UIO7: J6.23 (uio7), U5.35 (IOB30A/GCLKT_4)
TT_UO0: J7.19 (uo_out0), U5.11 (IOL29B/GCLKC_6)
TT_UO1: J7.17 (uo_out1), U5.13 (IOL45A/LPLL2_T_in)
TT_UO2: J7.15 (uo_out2), U5.15 (IOL47A/LPLL2_T_fb)
TT_UO3: J7.13 (uo_out3), U5.16 (IOL47B/LPLL2_C_fb)
TT_UO4: J7.9 (uo_out4), U5.17 (IOL49A)
TT_UO5: J7.7 (uo_out5), U5.18 (IOL49B)
TT_UO6: J7.5 (uo_out6), U5.19 (IOL51A)
TT_UO7: J7.3 (uo_out7), U5.20 (IOL51B)
USB_CC1: J1.A5 (CC1), R1.1
USB_CC2: J1.B5 (CC2), R2.1
USB_DN: J1.A7 (D-), J1.B7 (D-), U1.3 (I/O2), U1.4 (I/O2), U8.26 (GPIO18/USB_D-)
USB_DP: J1.A6 (D+), J1.B6 (D+), U1.1 (I/O1), U1.6 (I/O1), U8.27 (GPIO19/USB_D+)
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
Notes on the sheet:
1 USB-C power input, protection, current sense
2 Regulators: 5V -> 3.3V and 1.0V (as Tang Nano 20K)
5 LED strip driver (common-anode 5V strip: +5V, G, R, B)
3 FPGA GW2AR-18 (support circuit copied from Tang Nano 20K v3923)
4 FPGA config flash, 27 MHz clock, JTAG, expansion
9 ESP32-C3 (Wi-Fi/BLE, USB, I2C current sensor, FPGA JTAG + UART)
6 Digital mic (FFT mode) and IR receiver
10 Mechanical
8 Tiny Tapeout chip breakout socket (Hirose DF12, as TT demo board)
7 Analog mic -> Tiny Tapeout chip analog input (an0)
Power flags (rails driven through passives)
ledctl v1 - Music-sync LED controller. Labels with the same name are connected.
